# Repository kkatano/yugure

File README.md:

# Yugure

This project is currently primarily for experimental purposes. You are free to use the files in this project according to the license, but I do not recommend that use them as-is

## Feature
- 60% WKL
- O-ring mount (friction fit)
- Single piece tray case
- Designed for SLS 3D printing

## Context
- I've never made a WKL board before and wanted to try it out
- Experimenting with some concepts
 - Unique gasket post location and shape. Testing how they affect the typing feel
 - Design of weight in tray case. Exploring the size and location of weight that are effective in reducing unwanted hollow sound, rather than making the case heavier

## Parts Guide
- Case
  - Use the the files contained in `case` directory
  - `case.step` is the design of the case. Order it from a service that supports SLS 3D printing
  - `weight.dxf` is the design of the weight to be attached to the case. Order 1.5mm thick from laser cutting service
  - Use 6 * 5mm M2 screws to secure the board
- PCB
  - Use the the files contained in `production` directory
  - The files is designed for ordering on JLCPCB. If you are ordering from any other manufacturer, please modify it as necessary
- Plate
  - Use the dxf files contained in `plate` directory
  - Order 1.5mm thick from laser cutting service
- Daughterboard
  - Use the [b-ken-ko's daughterboard](https://github.com/xyzz/b-ken-ko)
  - Use 2 * 3mm M3 screws to secure the board
- O-ring
  - Material: Silicone
  - Durometer(Hardness): 50A
  - AS568 number: 262
  - CS(Thickness): 3.53mm
  - ID(Inner Diameter): 177.39mm
  - OD(Outer Diameter): 184.45mm

## Notes
- This project is experimental and is not designed for serious use like production run
- You may be able to adjust the typing feel by changing the position and size of the mounting post
- There is a mounting post under the blocker, which may be difficult to make with CNC machining
- The PCB design includes the [MX_Alps_Hybrid](https://github.com/ai03-2725/MX_Alps_Hybrid/tree/b2517004a92a2ea354670c713a1530817f9da6df) designed by ai03 as a submodule. It is distributed under the MIT license

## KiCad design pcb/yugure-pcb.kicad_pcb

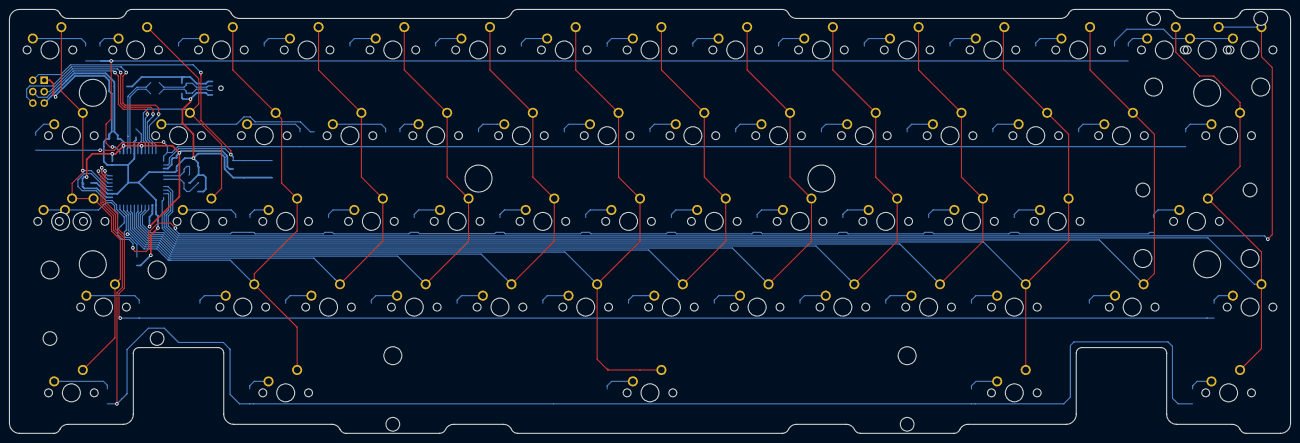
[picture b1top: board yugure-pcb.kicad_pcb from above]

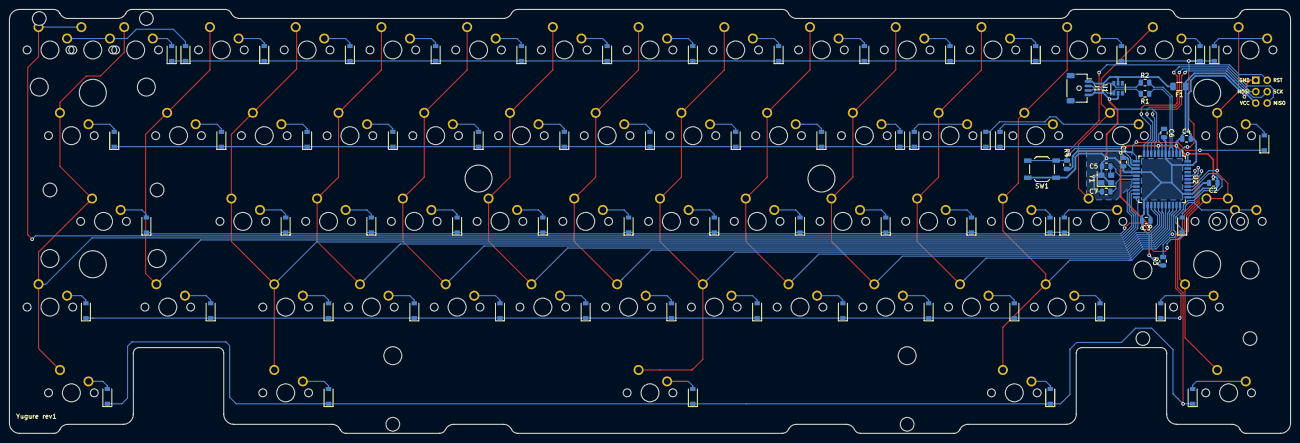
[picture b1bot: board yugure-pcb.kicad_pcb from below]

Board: 2 copper layers, 284.7 x 94.2 mm, 140 parts (78 on the bottom side), 95 nets.

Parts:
C1, C2, C3: 0.1u; C_0805_2012Metric
C4: 10u; C_0805_2012Metric
C5, C7: 22p; C_0805_2012Metric
C6: 1u; C_0805_2012Metric
D1, D2, D3, D4, D5, D6, D7, D8, D9, D10, D11, D12, D13, D14, D15, D16, D17, D18, D19, D20, D21, D22, D23, D24, D25, D26, D27, D28, D29, D30, D31, D32, D33, D34, D35, D36, D37, D38, D39, D40, D41, D42, D43, D44, D45, D46, D47, D48, D49, D50, D51, D52, D53, D54, D55, D56, D57, D58, D59, D60: 1N4148; D_SOD-123
F1: 500mA; Fuse_1206_3216Metric
J1: JST SH 4-pin; JST_SH_SM04B-SRSS-TB_1x04-1MP_P1.00mm_Horizontal
J2: AVR-ISP-6; ISP
MX1, MX2, MX3, MX4, MX5, MX6, MX7, MX8, MX9, MX10, MX11, MX12, MX13, MX14, MX15, MX18, MX19, MX20, MX21, MX22, MX23, MX24, MX25, MX26, MX27, MX28, MX29, MX33, MX34, MX35, MX36, MX37, MX38, MX39, MX40, MX41, MX42, MX43, MX46, MX47, MX48, MX49, MX50, MX51, MX52, MX53, MX54, MX55, MX57: 1u; MXOnly-1U-NoLED
MX16: 2u; MXOnly-2U-NoLED
MX17, MX30, MX58, MX59, MX61, MX62: 1.5u; MXOnly-1.5U-NoLED
MX31: 1.25u; MXOnly-1.25U-NoLED
MX32, MX56: 1.75u; MXOnly-1.75U-NoLED
MX44: 2.25u; MXOnly-2.25U-NoLED
MX45: 2.25u; MXOnly-2.25U-ReversedStabilizers-NoLED
MX60: 7u; MXOnly-7U-ReversedStabilizers-NoLED
R1, R2: 22; R_0805_2012Metric
R3, R4: 10k; R_0805_2012Metric
SW1: Reset; SW_SPST_TL3342
U1: SRV05-4; SOT-23-6
U2: ATmega32U4-AU; TQFP-44_10x10mm_P0.8mm
Y1: 16MHz; Crystal_SMD_3225-4Pin_3.2x2.5mm

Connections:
+5V: C1.1, C2.1, C3.1, C4.1, F1.1, J2.2, R4.2, U2.2, U2.7, U2.14, U2.24, U2.34, U2.44
/MCU_D+: R1.1, U2.4
/MCU_D-: R2.1, U2.3
COL0: MX1.2, MX17.2, MX31.2, MX32.2, MX45.2, MX58.2, U2.37
COL1: MX2.2, MX18.2, MX33.2, U2.8
COL2: MX3.2, MX19.2, MX34.2, MX46.2, MX59.2, U2.40
COL3: MX4.2, MX20.2, MX35.2, MX47.2, U2.32
COL4: MX5.2, MX21.2, MX36.2, MX48.2, U2.31
COL5: MX6.2, MX22.2, MX37.2, MX49.2, U2.30
COL6: MX7.2, MX23.2, MX38.2, MX50.2, MX60.2, U2.29
COL7: MX8.2, MX24.2, MX39.2, MX51.2, U2.28
COL8: MX9.2, MX25.2, MX40.2, MX52.2, U2.27
COL9: MX10.2, MX26.2, MX41.2, MX53.2, U2.26
COL10: MX11.2, MX27.2, MX42.2, MX54.2, U2.25
COL11: MX12.2, MX28.2, MX43.2, MX55.2, MX61.2, U2.22
COL12: MX13.2, MX29.2, MX56.2, U2.21
COL13: MX14.2, MX30.2, MX44.2, MX57.2, MX62.2, U2.20
COL14: MX15.2, MX16.2, U2.19
D+: J1.3, R1.2, U1.1
D-: J1.2, R2.2, U1.6
GND: C1.2, C2.2, C3.2, C4.2, C5.1, C6.2, C7.1, J1.4, J2.6, R3.1, SW1.1, U1.2, U2.5, U2.15, U2.23, U2.35, U2.43, Y1.2, Y1.4
MISO: J2.1, U2.11
MOSI: J2.4, U2.10
unnamed: C6.1, U2.6
unnamed: D1.2, MX1.1
unnamed: D2.2, MX2.1
unnamed: D3.2, MX3.1
unnamed: D4.2, MX4.1
unnamed: D5.2, MX5.1
unnamed: D6.2, MX6.1
unnamed: D7.2, MX7.1
unnamed: D8.2, MX8.1
unnamed: D9.2, MX9.1
unnamed: D10.2, MX10.1
unnamed: D11.2, MX11.1
unnamed: D12.2, MX12.1
unnamed: D13.2, MX13.1
unnamed: D14.2, MX14.1
unnamed: D15.2, MX15.1, MX16.1
unnamed: D16.2, MX17.1
unnamed: D17.2, MX18.1
unnamed: D18.2, MX19.1
unnamed: D19.2, MX20.1
unnamed: D20.2, MX21.1
unnamed: D21.2, MX22.1
unnamed: D22.2, MX23.1
unnamed: D23.2, MX24.1
unnamed: D24.2, MX25.1
unnamed: D25.2, MX26.1
unnamed: D26.2, MX27.1
unnamed: D27.2, MX28.1
unnamed: D28.2, MX29.1
unnamed: D29.2, MX30.1
unnamed: D30.2, MX31.1, MX32.1
unnamed: D31.2, MX33.1
unnamed: D32.2, MX34.1
unnamed: D33.2, MX35.1
unnamed: D34.2, MX36.1
unnamed: D35.2, MX37.1
unnamed: D36.2, MX38.1
unnamed: D37.2, MX39.1
unnamed: D38.2, MX40.1
unnamed: D39.2, MX41.1
unnamed: D40.2, MX42.1
unnamed: D41.2, MX43.1
unnamed: D42.2, MX44.1
unnamed: D43.2, MX45.1
unnamed: D44.2, MX46.1
unnamed: D45.2, MX47.1
unnamed: D46.2, MX48.1
unnamed: D47.2, MX49.1
unnamed: D48.2, MX50.1
unnamed: D49.2, MX51.1
unnamed: D50.2, MX52.1
unnamed: D51.2, MX53.1
unnamed: D52.2, MX54.1
unnamed: D53.2, MX55.1
unnamed: D54.2, MX56.1
unnamed: D55.2, MX57.1
unnamed: D56.2, MX58.1
unnamed: D57.2, MX59.1
unnamed: D58.2, MX60.1
unnamed: D59.2, MX61.1
unnamed: D60.2, MX62.1
unnamed: R3.2, U2.33
ROW0: D1.1, D2.1, D3.1, D4.1, D5.1, D6.1, D7.1, D8.1, D9.1, D10.1, D11.1, D12.1, D13.1, D14.1, D15.1, U2.1
ROW1: D16.1, D17.1, D18.1, D19.1, D20.1, D21.1, D22.1, D23.1, D24.1, D25.1, D26.1, D27.1, D28.1, D29.1, U2.12
ROW2: D30.1, D31.1, D32.1, D33.1, D34.1, D35.1, D36.1, D37.1, D38.1, D39.1, D40.1, D41.1, D42.1, U2.36
ROW3: D43.1, D44.1, D45.1, D46.1, D47.1, D48.1, D49.1, D50.1, D51.1, D52.1, D53.1, D54.1, D55.1, U2.39
ROW4: D56.1, D57.1, D58.1, D59.1, D60.1, U2.38
RST: J2.5, R4.1, SW1.2, U2.13
SCK: J2.3, U2.9
VBUS: F1.2, J1.1, U1.5
XTAL1: C7.2, U2.17, Y1.1
XTAL2: C5.2, U2.16, Y1.3

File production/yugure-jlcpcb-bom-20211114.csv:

Designator,Comment,Footprint,LCSC Part #
C1 C2 C3 ,0.1u,Capacitor_SMD:C_0805_2012Metric,C49678
C4 ,10u,Capacitor_SMD:C_0805_2012Metric,C15850
C5 C7 ,22p,Capacitor_SMD:C_0805_2012Metric,C1804
C6 ,1u,Capacitor_SMD:C_0805_2012Metric,C28323
D60 D59 D58 D57 D56 D55 D54 D53 D52 D51 D50 D49 D48 D47 D46 D45 D44 D43 D42 D41 D40 D39 D38 D37 D36 D35 D34 D33 D32 D31 D30 D29 D28 D27 D26 D25 D24 D23 D22 D21 D20 D19 D18 D17 D16 D15 D14 D13 D12 D11 D10 D9 D8 D7 D6 D5 D4 D3 D2 D1 ,1N4148,Diode_SMD:D_SOD-123,C81598
F1 ,500mA,Fuse:Fuse_1206_3216Metric,C70076
J1 ,JST SH 4-pin,Connector_JST:JST_SH_SM04B-SRSS-TB_1x04-1MP_P1.00mm_Horizontal,C160404
R1 R2 ,22,Resistor_SMD:R_0805_2012Metric,C17561
R4 R3 ,10k,Resistor_SMD:R_0805_2012Metric,C17414
SW1 ,Reset,Button_Switch_SMD:SW_SPST_TL3342,C318884
U1 ,SRV05-4,Package_TO_SOT_SMD:SOT-23-6,C85364
U2 ,ATmega32U4-AU,Package_QFP:TQFP-44_10x10mm_P0.8mm,C44854
Y1 ,16MHz,Crystal:Crystal_SMD_3225-4Pin_3.2x2.5mm,C13738

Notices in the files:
pcb/yugure-pcb.kicad_pcb:
Copyright © 2021 kkatano
